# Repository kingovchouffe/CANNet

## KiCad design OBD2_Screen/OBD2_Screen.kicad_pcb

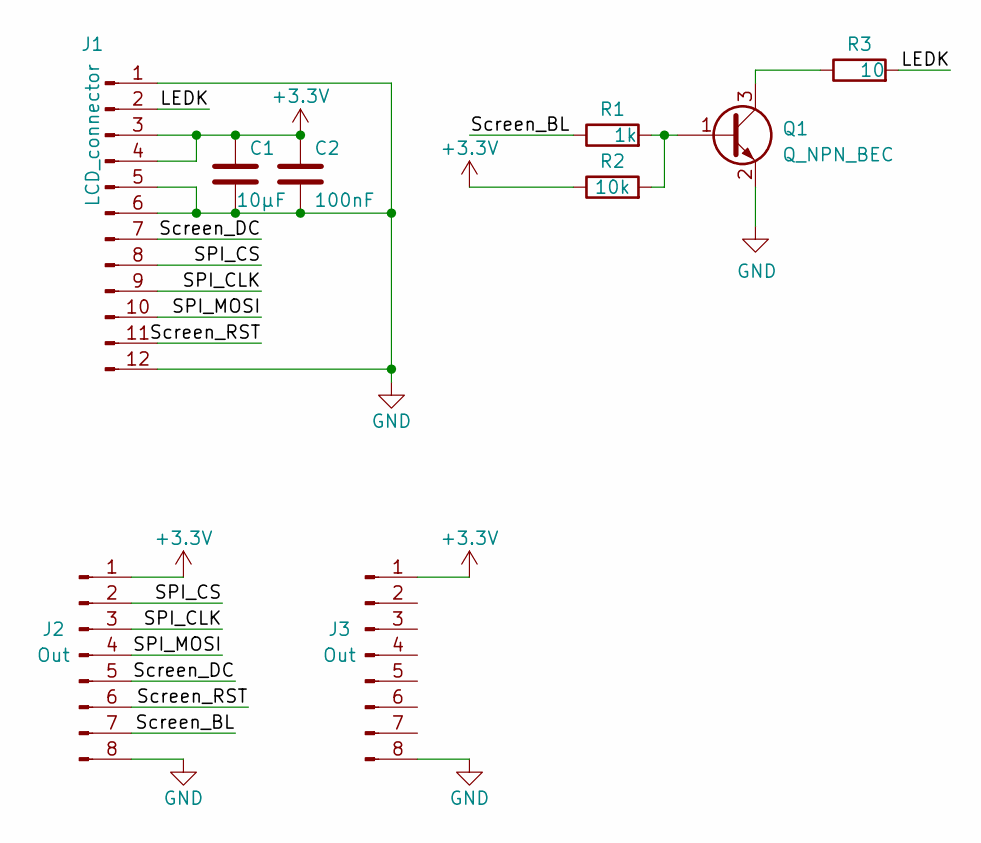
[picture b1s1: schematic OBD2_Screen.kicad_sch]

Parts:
C1: 10µF; C_0805_2012Metric
C2: 100nF; C_0603_1608Metric
J1: LCD_connector; FPC_12
J2, J3: Out; WR-MM Female 8pin
Q1: Q_NPN_BEC; SOT-23
R1: 1k; R_0603_1608Metric
R2: 10k; R_0603_1608Metric
R3: 10; R_0603_1608Metric

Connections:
+3V3: C1.2, C2.2, J1.3, J1.4, J2.1, J3.1, R2.1
/LEDK: J1.2, R3.2
/SPI_CLK: J1.9, J2.3
/SPI_CS: J1.8, J2.2
/SPI_MOSI: J1.10, J2.4
/Screen_BL: J2.7, R1.1
/Screen_DC: J1.7, J2.5
/Screen_RST: J1.11, J2.6
GND: C1.1, C2.1, J1.1, J1.5, J1.6, J1.12, J2.8, J3.8, Q1.2 (E)
unnamed: Q1.1 (B), R1.2, R2.2
unnamed: Q1.3 (C), R3.1

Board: 2 copper layers, 9 parts (0 on the bottom side), 11 nets, no tracks yet.

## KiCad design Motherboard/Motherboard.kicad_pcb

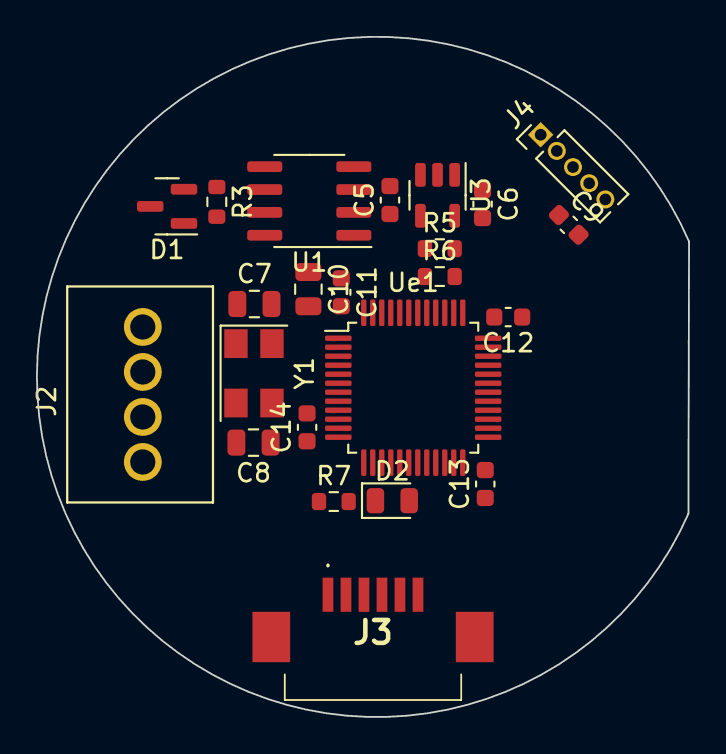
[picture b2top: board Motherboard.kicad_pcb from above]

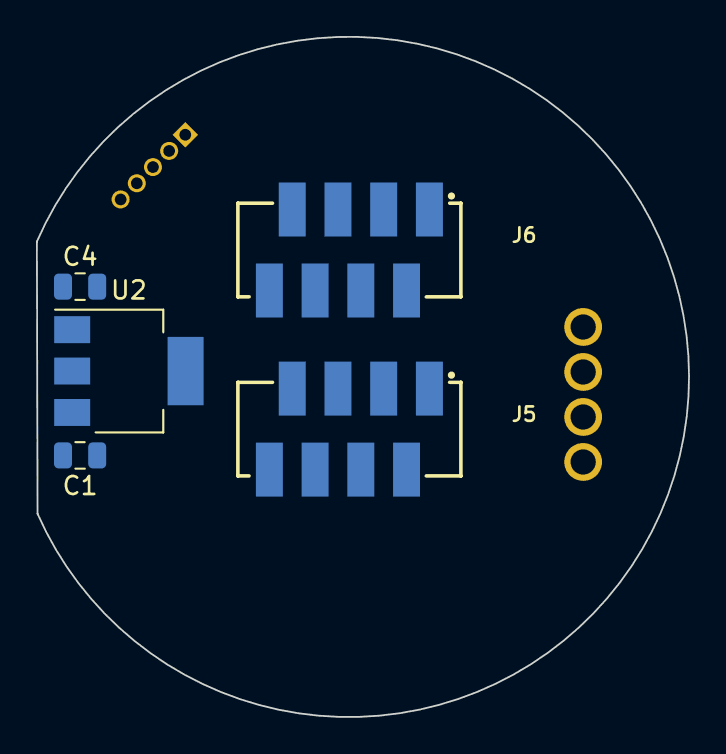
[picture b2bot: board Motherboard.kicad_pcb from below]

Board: 4 copper layers, 36.2 x 37.8 mm, 28 parts (5 on the bottom side), 23 nets, no tracks yet.

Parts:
C1, C4: 10u; C_0805_2012Metric
C5, C6, C11, C12, C13, C14: 100nF; C_0603_1608Metric
C7, C8: 18p; C_0805_2012Metric
C9: 100n; C_0603_1608Metric
C10: 10µF; C_0805_2012Metric
D1: D_TVS_x2_AAC; SOT-23
D2: LED_DEBUG; LED_0805_2012Metric
J2: IO; 691382000004
J3: Encoder; flex connector
J4: SWD_Connector; PinHeader_1x05_P1.27mm_Vertical
J5, J6: Out; WR-MM 8pin Male
R3, R7: 120; R_0603_1608Metric
R5, R6: 2k; R_0603_1608Metric
U1: SN65HVD232; SOIC-8_3.9x4.9mm_P1.27mm
U2: NCP1117-3.3_SOT223; SOT-223-3_TabPin2
U3: SOT-23-5
Ue1: STM32F302C6Tx; LQFP-48_7x7mm_P0.5mm
Y1: 8MHz; Crystal_SMD_5032-4Pin_5.0x3.2mm

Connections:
+3V3: C4.2, C5.2, C6.2, C10.2, C11.2, C12.2, C13.2, C14.2, J3.1, J4.1, J5.1, J6.1, R5.2, R6.2, U1.3 (VCC), U2.2 (VO), U3.5 (V_{CC}), Ue1.9 (VDDA), Ue1.24 (VDD), Ue1.36 (VDD), Ue1.48 (VDD)
+12V: C1.2, J2.1, U2.3 (VI)
/CANH: D1.1 (A1), J2.3, R3.2, U1.7 (CANH)
/CANL: D1.2 (A2), J2.4, R3.1, U1.6 (CANL)
/Encoder_A: J3.3, Ue1.11 (PA1)
/Encoder_B: J3.4, Ue1.12 (PA2)
/Encoder_Button: J3.5, Ue1.13 (PA3)
/I2C_SCL: R6.1, U3.1 (SCL), Ue1.42 (PB6)
/I2C_SDA: R5.1, U3.3 (SDA), Ue1.43 (PB7)
/RST: C9.1, J4.4, Ue1.7 (NRST)
/SPI_CLK: J5.3, Ue1.26 (PB13)
/SPI_CS: J5.2, Ue1.25 (PB12)
/SPI_MOSI: J5.4, Ue1.28 (PB15)
/SWCLK: J4.3, Ue1.37 (PA14)
/SWDIO: J4.2, Ue1.34 (PA13)
/Screen_BL: J5.7, Ue1.31 (PA10)
/Screen_DC: J5.5, Ue1.29 (PA8)
/Screen_RST: J5.6, Ue1.30 (PA9)
GND: C1.1, C4.1, C5.1, C6.1, C7.2, C8.2, C9.2, C10.1, C11.1, C12.1, C13.1, C14.1, D1.3 (common), J2.2, J3.2, J3.6, J4.5, J5.8, J6.8, R7.1, U1.2 (GND), U2.1 (GND), U3.2 (V_{SS}), Ue1.8 (VSSA), Ue1.23 (VSS), Ue1.35 (VSS), Ue1.47 (VSS), Y1.2, Y1.4
unnamed: D2.2 (A), Ue1.18 (PB0)
unnamed: D2.1 (K), R7.2
unnamed: C7.1, Ue1.5 (PF0), Y1.1
unnamed: C8.1, Ue1.6 (PF1), Y1.3
